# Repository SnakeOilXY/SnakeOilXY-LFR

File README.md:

# SnakeOilXY-LFR

SnakeOilXY-LFR (Large format FR4) is a complete redesign inspired by the [Voron 2.x](https://github.com/VoronDesign/Voron-2) with the goal of achieving better performance, scalability, reliability, and reduced maintenance. By incorporating FR4 for structural parts alongside printed components and utilizing a metal core reinforced design, it results in a more robust motion system that is less affected by the characteristics of the filament used in the printed parts. Furthermore, it is more suitable for large format machines.

## Project goals

- 4 motors coreXY kinematic.
- Zero-play Z joints with vibration damper built-in.
- 9mm belt on XY axis, 12mm belt on Z axis.
- Hybrid 3D printed + FR4 structural parts .
- AUX fan support.
- Active-ish chamber heater.
- Better support and reliability for MMU/filament-loader units. 
- Thermal expansion compensation bed mount

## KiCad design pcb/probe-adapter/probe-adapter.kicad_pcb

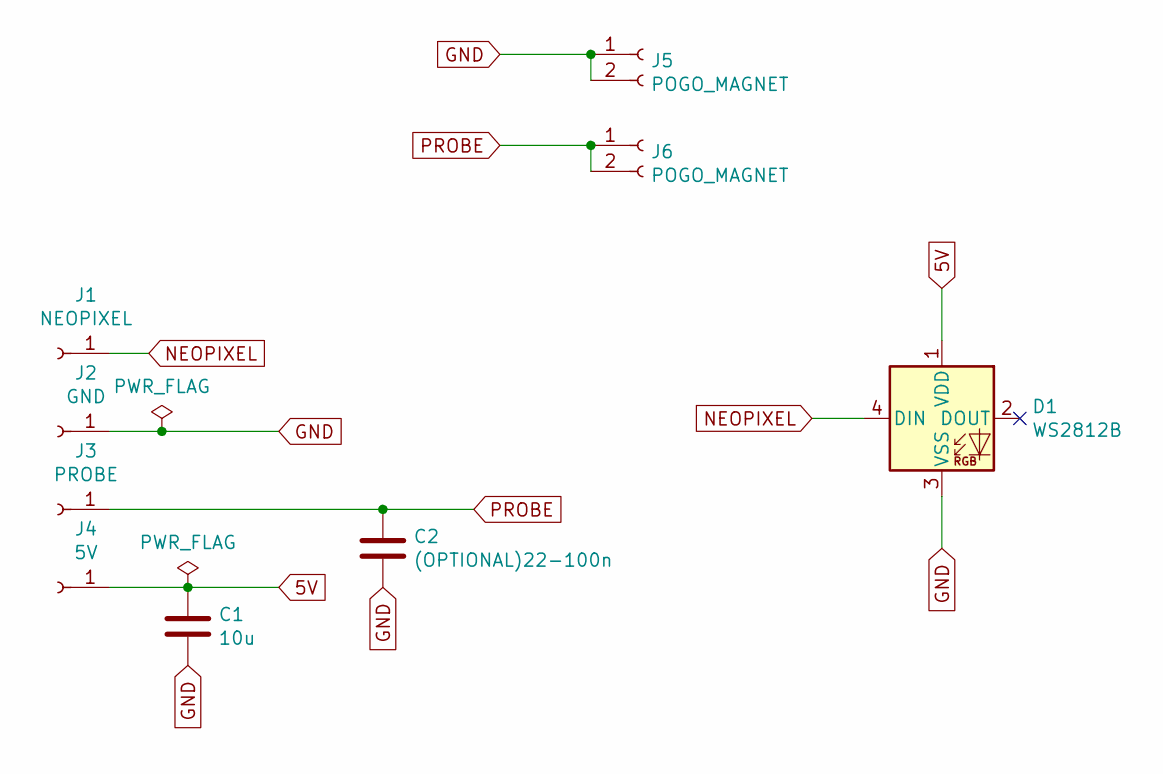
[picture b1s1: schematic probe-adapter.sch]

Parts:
C1: 10u; C_0805_2012Metric_Pad1.18x1.45mm_HandSolder
C2: (OPTIONAL)22-100n; C_0805_2012Metric_Pad1.18x1.45mm_HandSolder
D1: WS2812B; LED_WS2812B_PLCC4_5.0x5.0mm_P3.2mm
J1: NEOPIXEL; solder-pad
J2: GND; solder-pad
J3: PROBE; solder-pad
J4: 5V; solder-pad
J5, J6: POGO_MAGNET; pogo-magnet-2p

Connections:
5V: C1.1, D1.1 (VDD), J4.1
GND: C1.2, C2.2, D1.3 (VSS), J2.1, J5.1, J5.2
NEOPIXEL: D1.4 (DIN), J1.1
PROBE: C2.1, J3.1, J6.1, J6.2

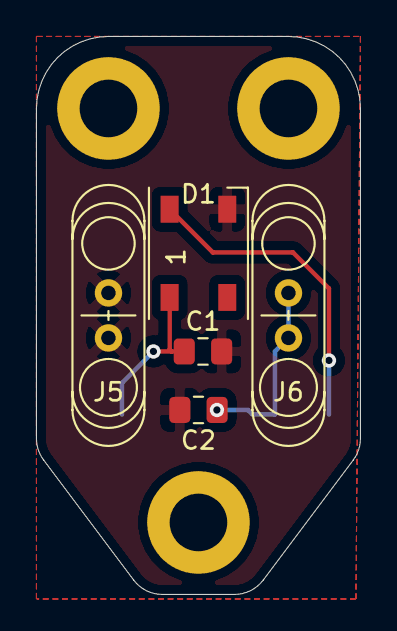
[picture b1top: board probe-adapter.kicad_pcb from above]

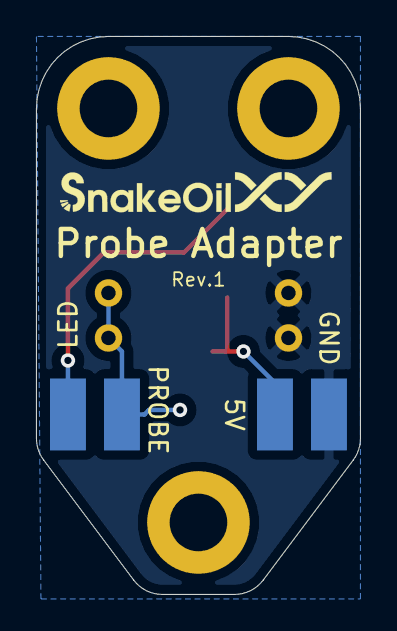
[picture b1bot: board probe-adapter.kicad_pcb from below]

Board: 2 copper layers, 18.0 x 31.0 mm, 9 parts (4 on the bottom side), 4 nets.

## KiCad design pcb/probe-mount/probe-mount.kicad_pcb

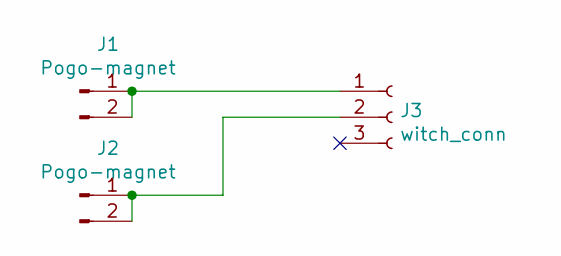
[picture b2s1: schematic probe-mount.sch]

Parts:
J1, J2: Pogo-magnet; pogo-magnet-2p
J3: witch_conn; Switch-limit-D2HW

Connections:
unnamed: J1.1, J1.2, J3.1
unnamed: J2.1, J2.2, J3.2

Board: 2 copper layers, 3 parts (2 on the bottom side), 2 nets, no tracks yet.

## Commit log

2023-06-29 init
2023-06-29 add back motor mount draf
2023-07-05 update back motor mounter
2023-07-12 add frame length caculator
2023-07-13 update z joint mounter
2023-07-24 sync: wip toolhead
2023-07-26 sync: probe-pcb
2023-08-02 sync : export gerber
2023-08-07 sync
2023-08-08 add 69-lite jigs and spacer
2023-08-10 test embed js
2023-08-10 test
2023-08-10 update frame caculator
2023-08-31 lite-69: add bed and bottom panel draft
2024-02-08 add panel profiles
2024-02-08 update draft layout
